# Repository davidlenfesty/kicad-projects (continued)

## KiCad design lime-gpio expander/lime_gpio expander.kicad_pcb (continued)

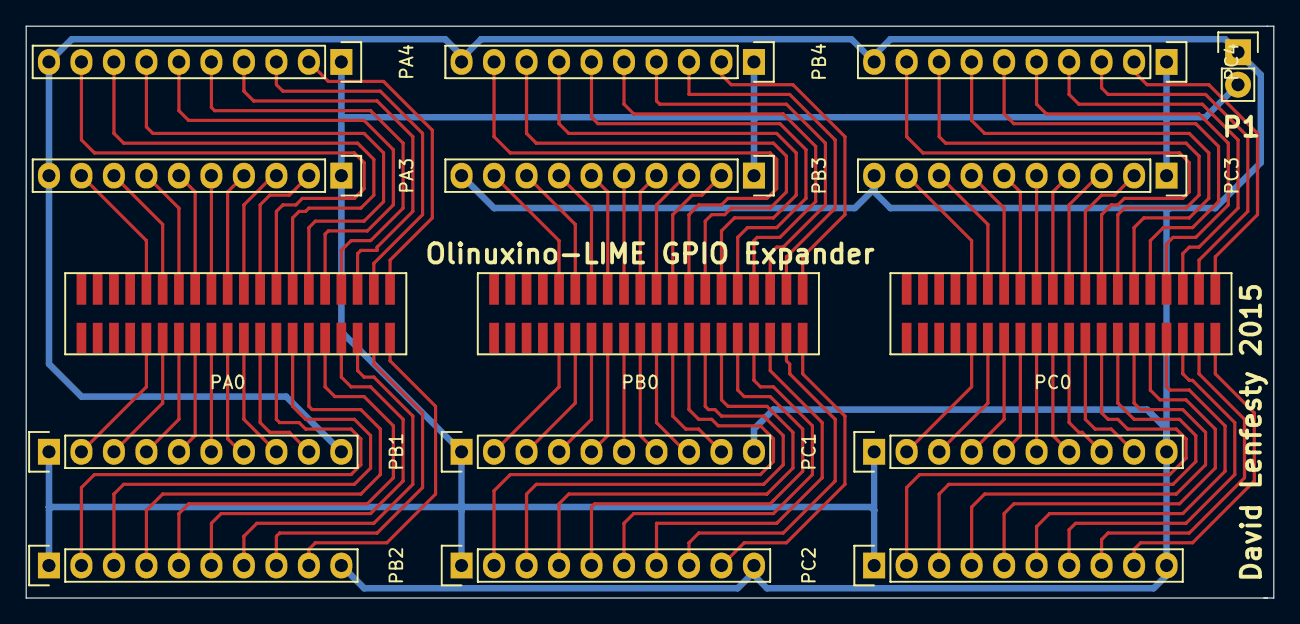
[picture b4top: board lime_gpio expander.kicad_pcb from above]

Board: 2 copper layers, 97.5 x 44.7 mm, 16 parts (0 on the bottom side), 98 nets.

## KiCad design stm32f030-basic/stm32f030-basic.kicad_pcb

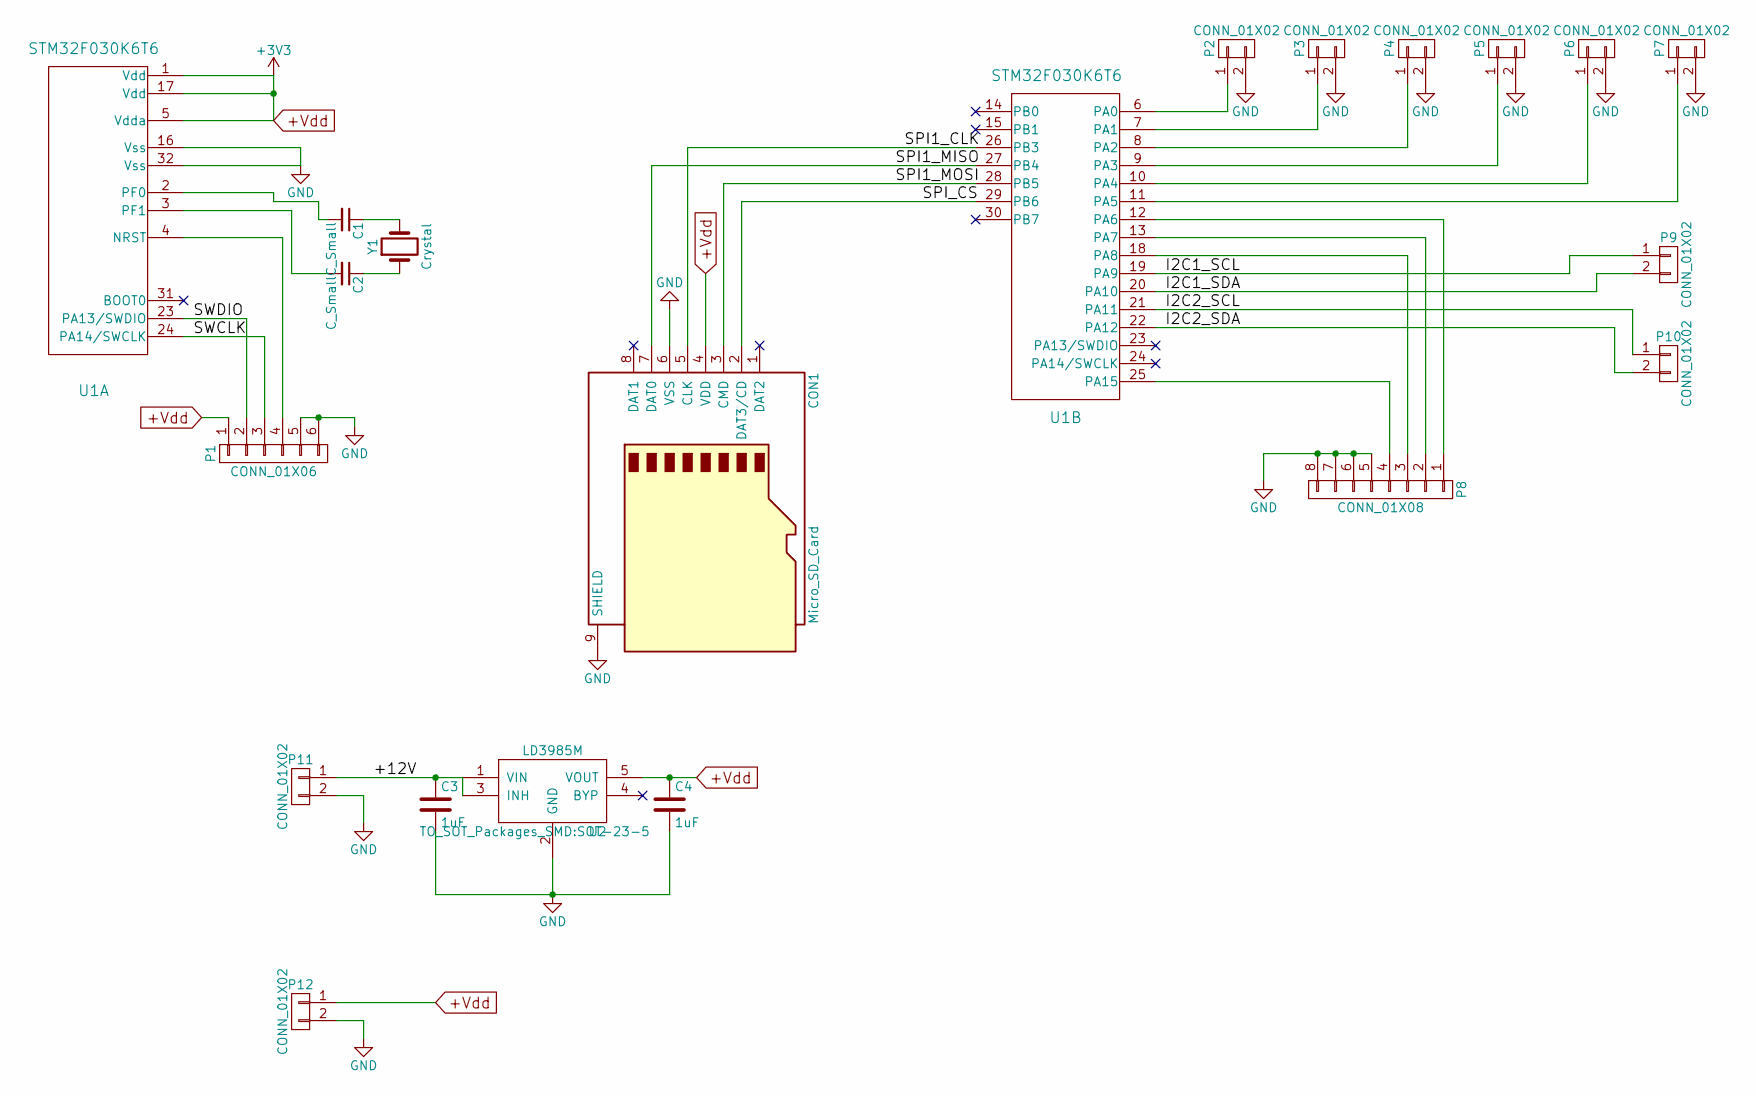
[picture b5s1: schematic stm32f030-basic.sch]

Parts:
C1, C2: C_Small; C_0805_HandSoldering
C3, C4: 1uF; C_0805_HandSoldering
CON1: Micro_SD_Card; microSD-5031821852
P1: CONN_01X06; Socket_Strip_Straight_1x06
P2, P3, P4, P5, P6, P7, P9, P10, P11, P12: CONN_01X02; Socket_Strip_Straight_1x02
P8: CONN_01X08; Socket_Strip_Straight_1x08
U1: STM32F030K6T6; LQFP-32_7x7mm_Pitch0.8mm
U2: LD3985M; SOT-23-5
Y1: Crystal; Crystal_SMD_HC49-SD_HandSoldering

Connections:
+Vdd: C4.1, CON1.4 (VDD), P1.1, P12.1, U1.1 (Vdd), U1.5 (Vdda), U1.17 (Vdd), U2.5 (VOUT)
/+12V: C3.1, P11.1, U2.1 (VIN), U2.3 (INH)
/I2C1_SCL: P9.1, U1.19 (PA9)
/I2C1_SDA: P9.2, U1.20 (PA10)
/I2C2_SCL: P10.1, U1.21 (PA11)
/I2C2_SDA: P10.2, U1.22 (PA12)
/SPI1_CLK: CON1.5 (CLK), U1.26 (PB3)
/SPI1_MISO: CON1.7 (DAT0), U1.27 (PB4)
/SPI1_MOSI: CON1.3 (CMD), U1.28 (PB5)
/SPI_CS: CON1.2 (DAT3/CD), U1.29 (PB6)
/SWCLK: P1.3, U1.24 (PA14/SWCLK)
/SWDIO: P1.2, U1.23 (PA13/SWDIO)
GND: C3.2, C4.2, CON1.6 (VSS), CON1.9 (SHIELD), P1.5, P1.6, P2.2, P3.2, P4.2, P5.2, P6.2, P7.2, P8.5, P8.6, P8.7, P8.8, P11.2, P12.2, U1.16 (Vss), U1.32 (Vss), U2.2 (GND)
unnamed: C1.1, Y1.2
unnamed: C1.2, U1.2 (PF0)
unnamed: C2.1, Y1.1
unnamed: C2.2, U1.3 (PF1)
unnamed: P1.4, U1.4 (NRST)
unnamed: P2.1, U1.6 (PA0)
unnamed: P3.1, U1.7 (PA1)
unnamed: P4.1, U1.8 (PA2)
unnamed: P5.1, U1.9 (PA3)
unnamed: P6.1, U1.10 (PA4)
unnamed: P7.1, U1.11 (PA5)
unnamed: P8.1, U1.12 (PA6)
unnamed: P8.2, U1.13 (PA7)
unnamed: P8.3, U1.18 (PA8)
unnamed: P8.4, U1.25 (PA15)

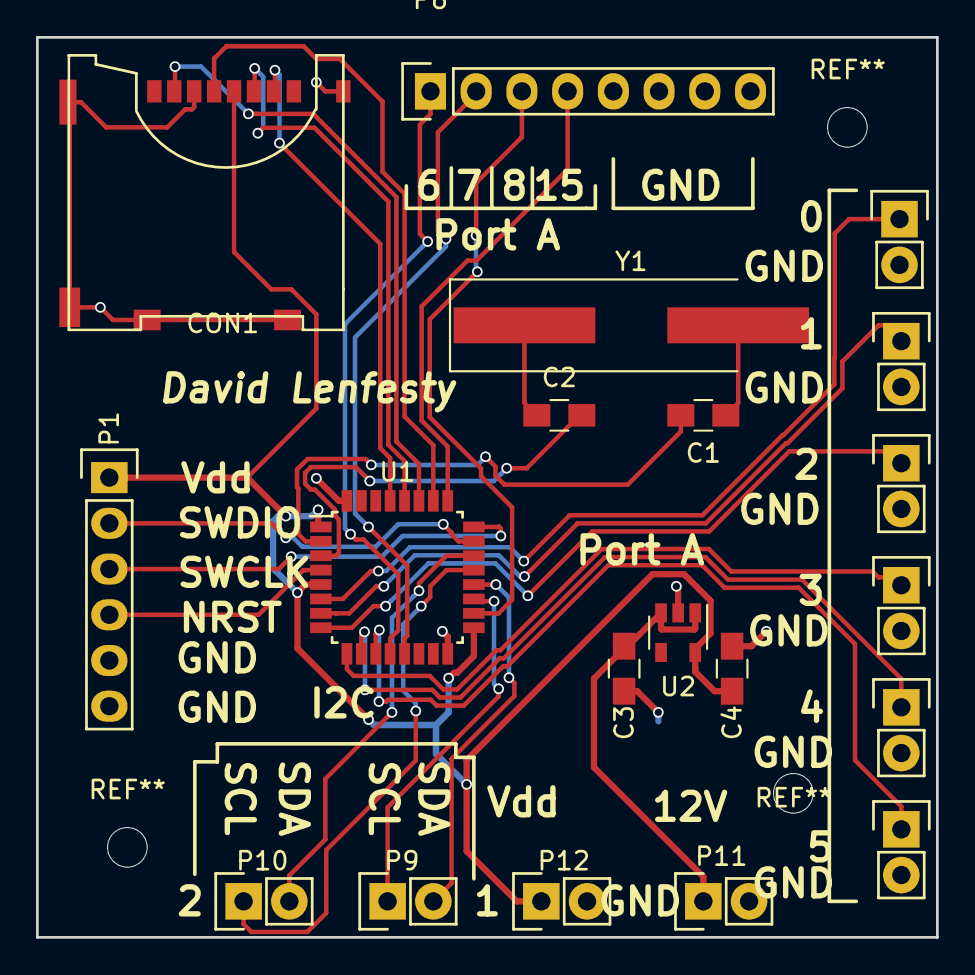
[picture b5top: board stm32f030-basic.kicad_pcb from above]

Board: 2 copper layers, 50.0 x 50.0 mm, 20 parts (0 on the bottom side), 28 nets.
